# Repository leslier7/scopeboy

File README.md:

# scopeboy
Polished version of the ScopeBoy project started in ECE5730

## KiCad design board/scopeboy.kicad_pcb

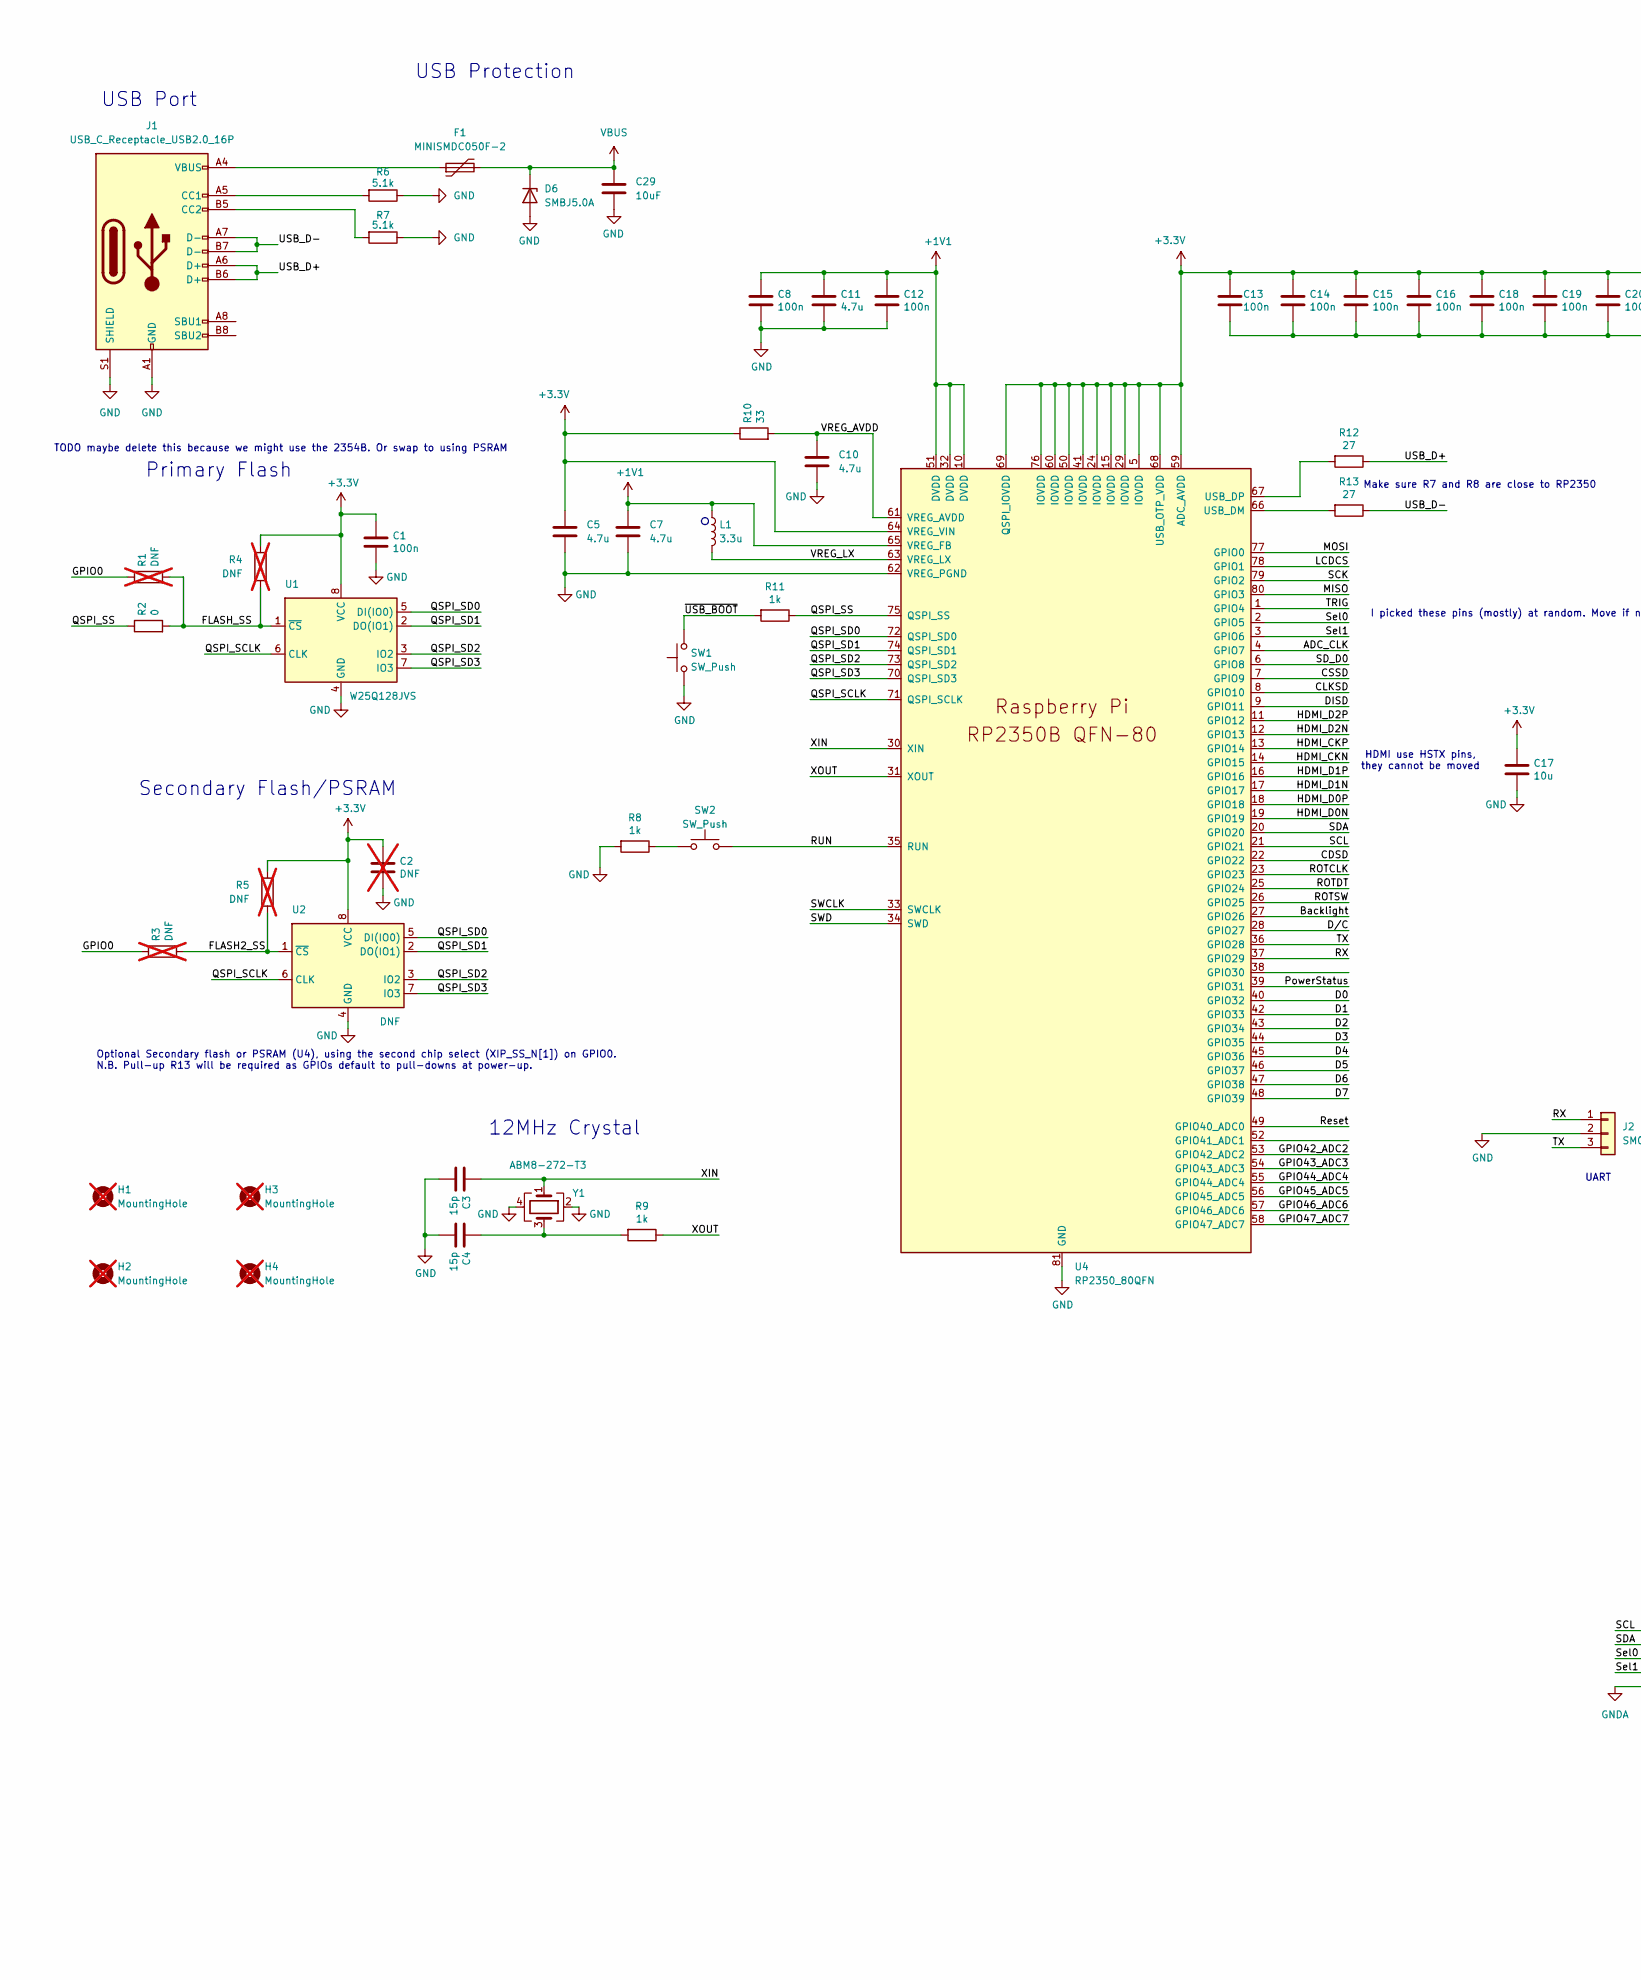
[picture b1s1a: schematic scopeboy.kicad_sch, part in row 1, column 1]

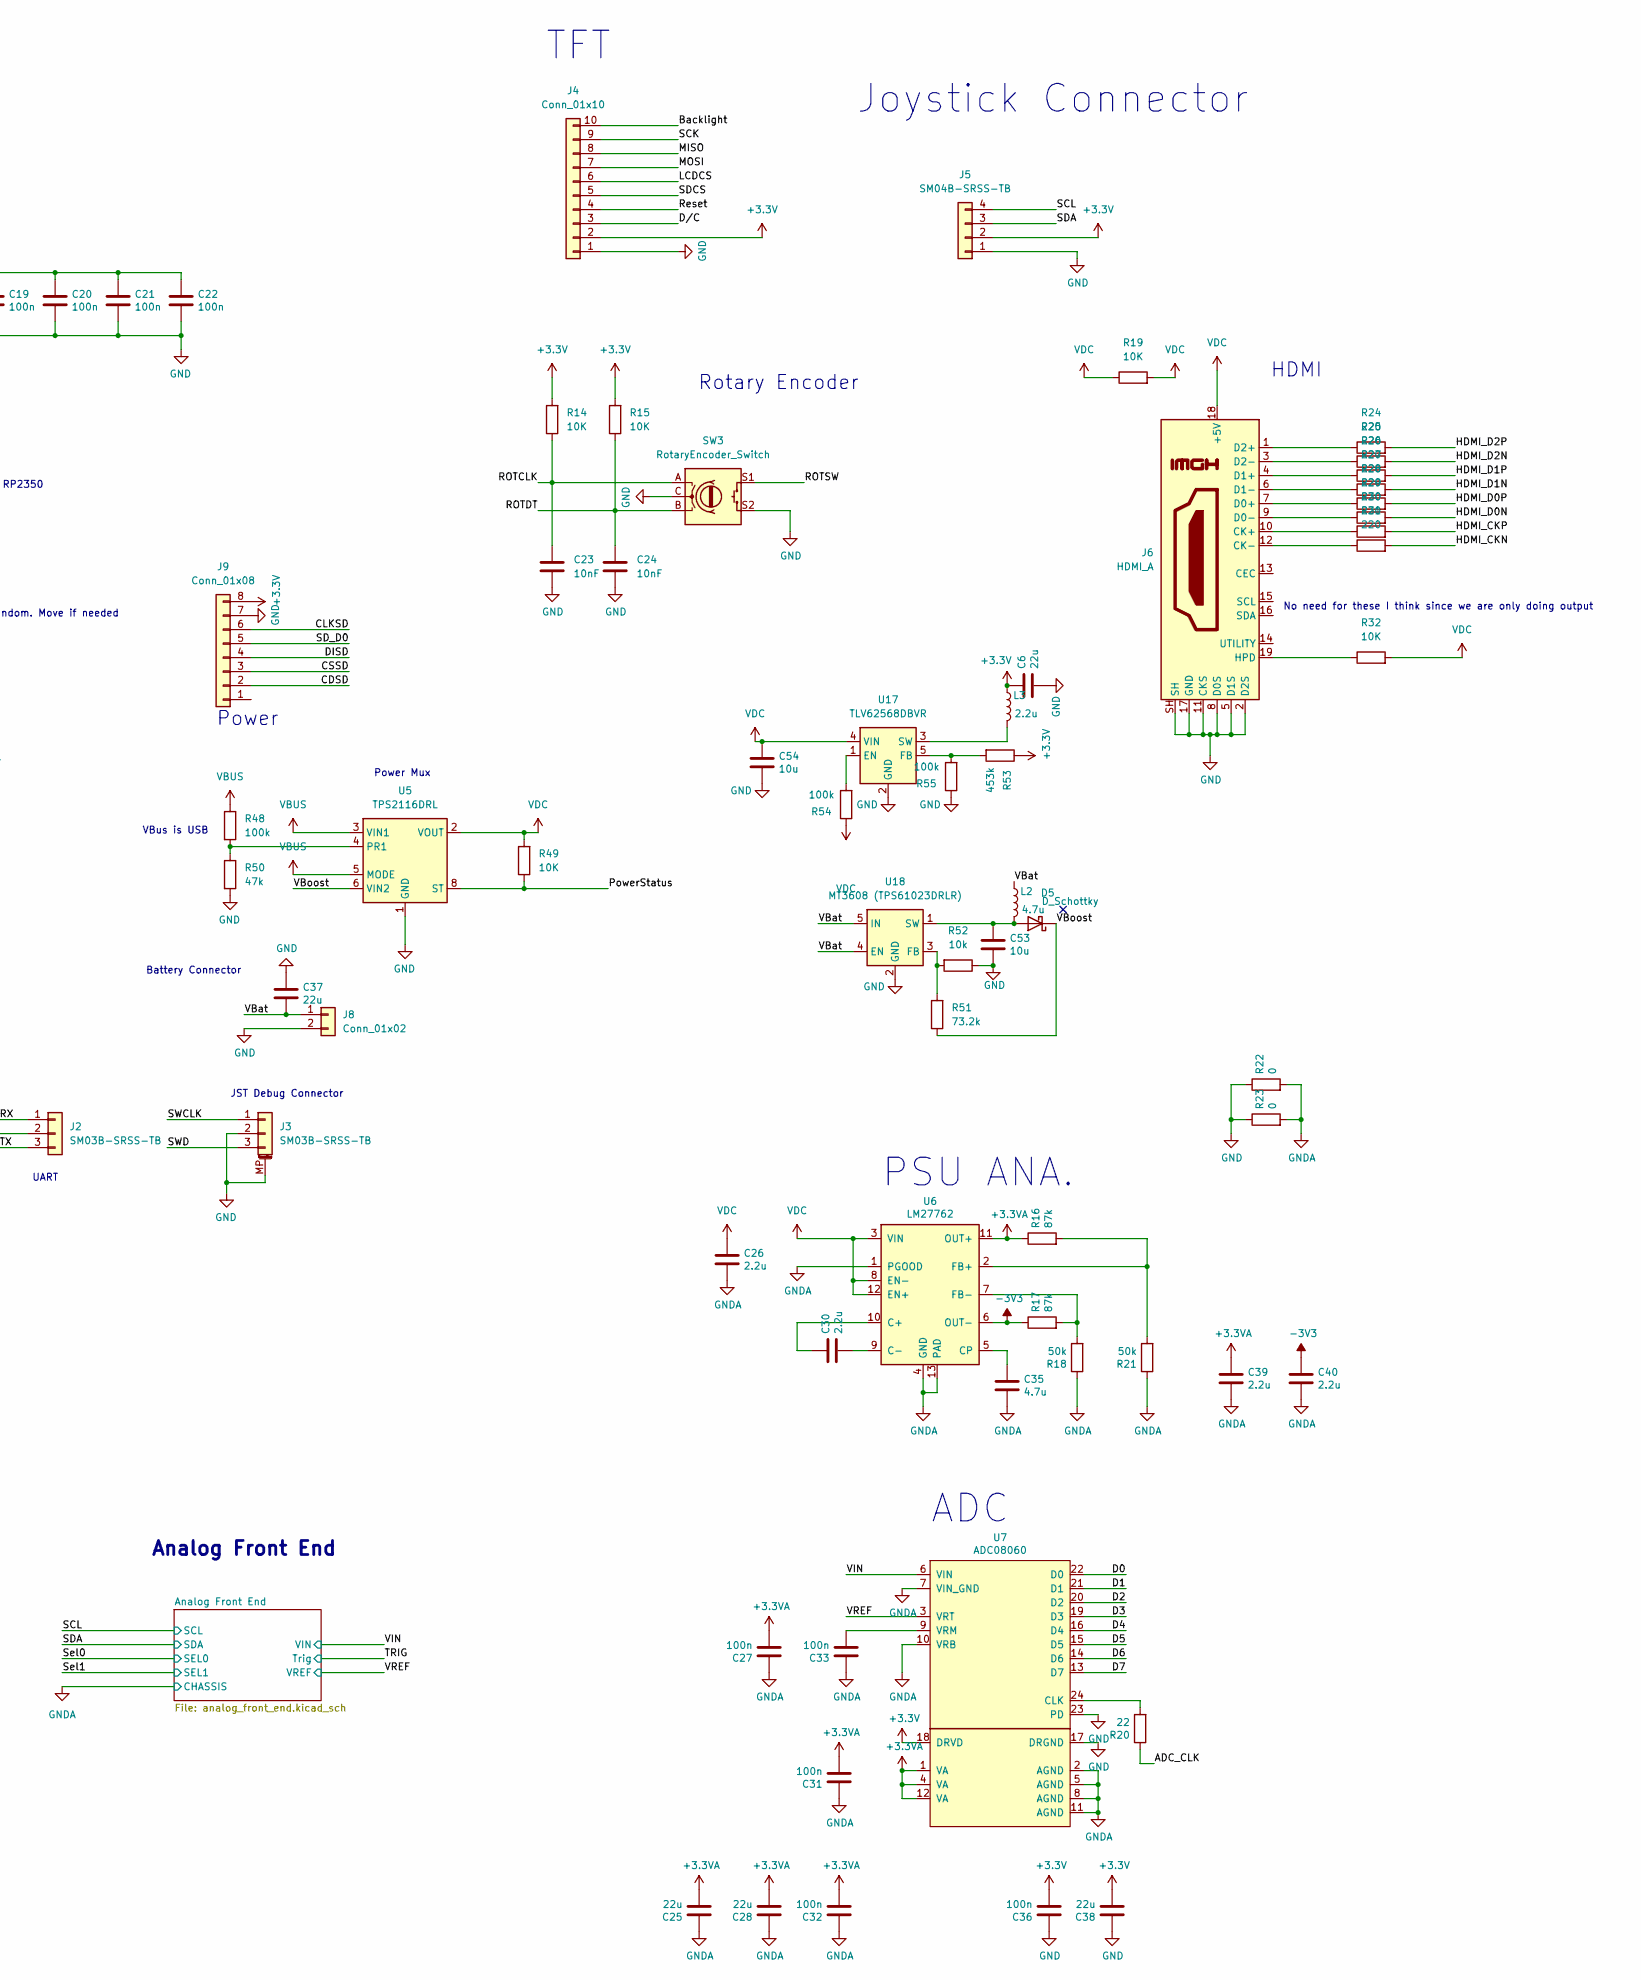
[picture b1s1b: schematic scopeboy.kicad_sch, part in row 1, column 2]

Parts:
C1, C8, C12, C13, C14, C15, C16, C18, C19, C20, C21, C22: 100n; C_0402_1005Metric; MFR. Part # AC0402JRNPO9BN100
C2: DNF; C_0402_1005Metric; not fitted
C3, C4: 15p; C_0402_1005Metric; MFR. Part # GJM1555C1H150GB01D
C5, C7: 4.7u; C_0402_1005Metric_small_pads; MFR. Part # CL05A475MP5NRNC
C6, C37: 22u; C_0805_2012Metric; MFR. Part # CL21A226MQQNNNE
C10, C11: 4.7u; C_0402_1005Metric; MFR. Part # CL05A475MP5NRNC
C17, C53, C54: 10u; C_0805_2012Metric; MFR. Part # CL21A106KOQNNNE
C23, C24: 10nF; C_0603_1608Metric; MFR. Part # CL10B103KB8NNNC; LCSC Part # C1589
C25, C28, C38: 22u; C_0603_1608Metric; MFR. Part # CL10A226MQ8NRNC; LCSC Part # C59461
C26, C30, C39, C40: 2.2u; C_0603_1608Metric; MFR. Part # CL10A225KO8NNNC; LCSC Part # C23630
C27, C31, C32, C33, C36: 100n; C_0603_1608Metric; MFR. Part # CC0603KRX7R9BB104; LCSC Part # C14663
C29: 10uF; C_1206_3216Metric; MFR. Part # TMK316BJ106KL-T
C35: 4.7u; C_0603_1608Metric; MFR. Part # CL10A475KO8NNNC; LCSC Part # C19666
D5: D_Schottky; D_SMA; MFR. Part # SS14
D6: SMBJ5.0A; D_SMB; MFR. Part # SMBJ5.0A
F1: MINISMDC050F-2; Fuse_1812_4532Metric; MFR. Part # MINISMDC050F-2
H1, H2, H3, H4: MountingHole; MountingHole_3.2mm_M3_Pad_TopBottom; not fitted
J1: USB_C_Receptacle_USB2.0_16P; USB_C_Receptacle_GCT_USB4105-xx-A_16P_TopMnt_Horizontal; MFR. Part # USB4105-GF-A
J2: SM03B-SRSS-TB; JST_SH_SM03B-SRSS-TB_1x03-1MP_P1.00mm_Horizontal; MFR. Part # SM03B-SRSS-TB(LF)(SN); LCSC Part # C160403
J3: SM03B-SRSS-TB; JST_SH_SM03B-SRSS-TB_1x03-1MP_P1.00mm_Horizontal
J4: Conn_01x10; PinHeader_1x10_P2.54mm_Vertical
J5: SM04B-SRSS-TB; JST_SH_SM04B-SRSS-TB_1x04-1MP_P1.00mm_Horizontal; MFR. Part # SM04B-SRSS-TB(LF)(SN); LCSC Part # C160404
J6: HDMI_A; HDMI_A_Molex_208658-1001_Horizontal; MFR. Part # 2086581001
J8: Conn_01x02; JST_PH_S2B-PH-SM4-TB_1x02-1MP_P2.00mm_Horizontal; MFR. Part # S2B-PH-SM4-TB(LF)(SN)
J9: Conn_01x08; PinHeader_1x08_P2.54mm_Vertical
L1: 3.3u; L_pol_2016; MFR. Part # SRN4018TA-3R3M
L2: 4.7u; L_Bourns-SRN4018; MFR. Part # SRN4018TA-4R7M
L3: 2.2u; L_Bourns-SRN4018; MFR. Part # SRN4018-2R2M
R1, R3, R4, R5: DNF; R_0402_1005Metric; not fitted
R2: 0; R_0402_1005Metric; MFR. Part # RC0402JR-070RL
R6, R7: 5.1k; R_1206_3216Metric; MFR. Part # CRCW12065K10FKEA
R8, R9, R11: 1k; R_0402_1005Metric; MFR. Part # CRCW04021K00FKED
R10: 33; R_0402_1005Metric; MFR. Part # RC0402JR-0733RL
R12, R13: 27; R_0402_1005Metric; MFR. Part # RC0402JR-0727RL
R14, R15, R19, R32, R49: 10K; R_0603_1608Metric; MFR. Part # RC0603FR-0710KL
R16, R17: 87k; R_0603_1608Metric; MFR. Part # 0603WAF8202T5E; LCSC Part # C23254
R18, R21: 50k; R_0603_1608Metric; MFR. Part # 0603WAF1503T5E; LCSC Part # C22807
R20: 22; R_0603_1608Metric; MFR. Part # 0603WAF220JT5E; LCSC Part # C23345
R22, R23: 0; R_0603_1608Metric; MFR. Part # 0603WAF0000T5E; LCSC Part # C21189
R24, R25, R26, R27, R28, R29, R30, R31: 220; R_0603_1608Metric; MFR. Part # CRGCQ0603J220R
R48, R54, R55: 100k; R_0603_1608Metric; MFR. Part # RC0603FR-07100KL
R50: 47k; R_0603_1608Metric; MFR. Part # RC0603FR-0747KL
R51: 73.2k; R_0603_1608Metric; MFR. Part # RMCF0603FT73K2
R52: 10k; R_0603_1608Metric; MFR. Part # RC0603FR-0710KL
R53: 453k; R_0603_1608Metric; MFR. Part # CRCW0603453KFKEAC
SW1, SW2: SW_Push; SW_Push_1P1T_NO_Vertical_Wuerth_434133025816
SW3: RotaryEncoder_Switch; PEC11L4115FS0020; MFR. Part # PEC11L4115FS0020
U1: W25Q128JVS; SOIC-8_5.23x5.23mm_P1.27mm; MFR. Part # W25Q128JVS
U2: DNF; SOIC-8_5.23x5.23mm_P1.27mm
U4: RP2350_80QFN; RP2350-QFN-80-1EP_10x10_P0.4mm_EP3.4x3.4mm_ThermalVias; MFR. Part # RP2354B
U5: TPS2116DRL; SOT-583-8; MFR. Part # TPS2116DRLR
U6: LM27762; WSON-12-1EP_3x2mm_P0.5mm_EP1x2.65_ThermalVias; MFR. Part # LM27762DSSR; LCSC Part # C473398
U7: ADC08060; TSSOP-24_4.4x7.8mm_P0.65mm; MFR. Part # TI ADC08060CIMT/NOPB; LCSC Part # C701069
U17: TLV62568DBVR; SOT-23-5; MFR. Part # TLV62568DBVR
U18: MT3608 (TPS61023DRLR); SOT-23-6; MFR. Part # MT3608
Y1: ABM8-272-T3; Crystal_SMD_3225-4Pin_3.2x2.5mm; MFR. Part # ABM8-272-T3

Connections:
+1V1: C7.1, C8.1, C11.1, C12.1, L1.1, U4.10 (DVDD), U4.32 (DVDD), U4.51 (DVDD), U4.65 (VREG_FB)
+3.3V: C1.1, C2.1, C5.1, C6.1, C13.1, C14.1, C15.1, C16.1, C17.1, C18.1, C19.1, C20.1, C21.1, C22.1, C36.2, C38.2, J4.2, J5.2, J9.8, L3.1, R4.1, R5.1, R10.1, R14.2, R15.2, R53.1, U1.8 (VCC), U2.8 (VCC), U4.5 (IOVDD), U4.15 (IOVDD), U4.24 (IOVDD), U4.29 (IOVDD), U4.41 (IOVDD), U4.50 (IOVDD), U4.59 (ADC_AVDD), U4.60 (IOVDD), U4.64 (VREG_VIN), U4.68 (USB_OTP_VDD), U4.69 (QSPI_IOVDD), U4.76 (IOVDD), U7.18 (DRVD)
+3.3VA: C25.2, C27.2, C28.2, C31.2, C32.2, C39.1, R16.1, U6.11 (OUT+), U7.1 (VA), U7.4 (VA), U7.12 (VA); also elsewhere on the board
-3V3: C40.1, R17.1, U6.6 (OUT-); also elsewhere on the board
/ADC_CLK: R20.1, U4.4 (GPIO7)
/Backlight: J4.10, U4.27 (GPIO26)
/CDSD: J9.2, U4.22 (GPIO22)
/CLKSD: J9.6, U4.8 (GPIO10)
/CSSD: J9.3, U4.7 (GPIO9)
/D0: U4.40 (GPIO32), U7.22 (D0)
/D1: U4.42 (GPIO33), U7.21 (D1)
/D2: U4.43 (GPIO34), U7.20 (D2)
/D3: U4.44 (GPIO35), U7.19 (D3)
/D4: U4.45 (GPIO36), U7.16 (D4)
/D5: U4.46 (GPIO37), U7.15 (D5)
/D6: U4.47 (GPIO38), U7.14 (D6)
/D7: U4.48 (GPIO39), U7.13 (D7)
/DISD: J9.4, U4.9 (GPIO11)
/D/C: J4.3, U4.28 (GPIO27)
/FLASH2_SS: R3.2, R5.2, U2.1 (~CS)
/FLASH_SS: R1.2, R2.2, R4.2, U1.1 (~CS)
/GPIO0: R1.1, R3.1
/GPIO42_ADC2: U4.53 (GPIO42_ADC2)
/GPIO43_ADC3: U4.54 (GPIO43_ADC3)
/GPIO44_ADC4: U4.55 (GPIO44_ADC4)
/GPIO45_ADC5: U4.56 (GPIO45_ADC5)
/GPIO46_ADC6: U4.57 (GPIO46_ADC6)
/GPIO47_ADC7: U4.58 (GPIO47_ADC7)
/HDMI_CKN: R31.2, U4.14 (GPIO15)
/HDMI_CKP: R30.2, U4.13 (GPIO14)
/HDMI_D0N: R29.2, U4.19 (GPIO19)
/HDMI_D0P: R28.2, U4.18 (GPIO18)
/HDMI_D1N: R27.2, U4.17 (GPIO17)
/HDMI_D1P: R26.2, U4.16 (GPIO16)
/HDMI_D2N: R25.2, U4.12 (GPIO13)
/HDMI_D2P: R24.2, U4.11 (GPIO12)
/LCDCS: J4.6, U4.78 (GPIO1)
/MISO: J4.8, U4.80 (GPIO3)
/MOSI: J4.7, U4.77 (GPIO0)
/PowerStatus: R49.1, U4.39 (GPIO31), U5.8 (ST)
/QSPI_SCLK: U1.6 (CLK), U2.6 (CLK), U4.71 (QSPI_SCLK)
/QSPI_SD0: U1.5 (DI(IO0)), U2.5 (DI(IO0)), U4.72 (QSPI_SD0)
/QSPI_SD1: U1.2 (DO(IO1)), U2.2 (DO(IO1)), U4.74 (QSPI_SD1)
/QSPI_SD2: U1.3 (IO2), U2.3 (IO2), U4.73 (QSPI_SD2)
/QSPI_SD3: U1.7 (IO3), U2.7 (IO3), U4.70 (QSPI_SD3)
/QSPI_SS: R2.1, R11.1, U4.75 (QSPI_SS)
/ROTCLK: C23.1, R14.1, SW3.A, U4.23 (GPIO23)
/ROTDT: C24.1, R15.1, SW3.B, U4.25 (GPIO24)
/ROTSW: SW3.S1, U4.26 (GPIO25)
/RUN: SW2.2, U4.35 (RUN)
/RX: J2.1, U4.37 (GPIO29)
/Reset: J4.4, U4.49 (GPIO40_ADC0)
/SCK: J4.9, U4.79 (GPIO2)
/SCL: J5.4, U4.21 (GPIO21); also elsewhere on the board
/SDA: J5.3, U4.20 (GPIO20); also elsewhere on the board
/SDCS: J4.5
/SD_D0: J9.5, U4.6 (GPIO8)
/SWCLK: J3.1, U4.33 (SWCLK)
/SWD: J3.3, U4.34 (SWD)
/Sel0: U4.2 (GPIO5); also elsewhere on the board
/Sel1: U4.3 (GPIO6); also elsewhere on the board
/TRIG: U4.1 (GPIO4); also elsewhere on the board
/TX: J2.3, U4.36 (GPIO28)
/USB_D+: J1.A6 (D+), J1.B6 (D+), R12.1
/USB_D-: J1.A7 (D-), J1.B7 (D-), R13.1
/VBat: C37.2, J8.1, L2.1, U18.4 (EN), U18.5 (IN)
/VBoost: D5.1 (K), R51.1, U5.6 (VIN2)
/VIN: U7.6 (VIN); also elsewhere on the board
/VREF: U7.3 (VRT); also elsewhere on the board
/VREG_AVDD: C10.1, R10.2, U4.61 (VREG_AVDD)
/VREG_LX: L1.2, U4.63 (VREG_LX)
/XIN: C3.1, U4.30 (XIN), Y1.1
/XOUT: R9.1, U4.31 (XOUT)
/~USB_BOOT: R11.2, SW1.2
GND: C1.2, C2.2, C3.2, C4.2, C5.2, C6.2, C7.2, C8.2, C10.2, C11.2, C12.2, C13.2, C14.2, C15.2, C16.2, C17.2, C18.2, C19.2, C20.2, C21.2, C22.2, C23.2, C24.2, C29.1, C36.1, C37.1, C38.1, C53.2, C54.2, D6.2 (A), J1.A1 (GND), J1.A12 (GND), J1.B1 (GND), J1.B12 (GND), J1.S1 (SHIELD), J2.2, J3.2, J3.MP (MountPin), J4.1, J5.1, J6.2 (D2S), J6.5 (D1S), J6.8 (D0S), J6.11 (CKS), J6.17 (GND), J6.SH, J8.2, J9.7, R6.1, R7.1, R8.2, R22.1, R23.1, R50.2, R52.1, R55.1, SW1.1, SW3.C, SW3.S2, U1.4 (GND), U2.4 (GND), U4.62 (VREG_PGND), U4.81 (GND), U5.1 (GND), U7.17 (DRGND), U7.23 (PD), U17.2 (GND), U18.2 (GND), Y1.2, Y1.4
GNDA: C25.1, C26.2, C27.1, C28.1, C31.1, C32.1, C33.1, C35.2, C39.2, C40.2, R18.1, R21.1, R22.2, R23.2, U6.1 (PGOOD), U6.4 (GND), U6.13 (PAD), U7.2 (AGND), U7.5 (AGND), U7.7 (VIN_GND), U7.8 (AGND), U7.10 (VRB), U7.11 (AGND); also elsewhere on the board
unnamed: C4.1, R9.2, Y1.3
unnamed: C53.1, D5.2 (A), L2.2, U18.1 (SW)
unnamed: F1.1, J1.A4 (VBUS), J1.A9 (VBUS), J1.B4 (VBUS), J1.B9 (VBUS)
unnamed: J1.A5 (CC1), R6.2
unnamed: J1.B5 (CC2), R7.2
unnamed: J6.10 (CK+), R30.1
unnamed: J6.12 (CK-), R31.1
unnamed: J6.7 (D0+), R28.1
unnamed: J6.9 (D0-), R29.1
unnamed: J6.4 (D1+), R26.1
unnamed: J6.6 (D1-), R27.1
unnamed: J6.1 (D2+), R24.1
unnamed: J6.3 (D2-), R25.1
unnamed: J6.19 (HPD), R32.1
unnamed: R8.1, SW2.1
unnamed: R13.2, U4.66 (USB_DM)
unnamed: R12.2, U4.67 (USB_DP)
unnamed: R48.2, R50.1, U5.4 (PR1)
unnamed: C30.1, U6.10 (C+)
unnamed: C30.2, U6.9 (C-)
unnamed: C35.1, U6.5 (CP)
unnamed: R16.2, R21.2, U6.2 (FB+)
unnamed: R17.2, R18.2, U6.7 (FB-)
unnamed: R20.2, U7.24 (CLK)
unnamed: C33.2, U7.9 (VRM)
unnamed: R54.2, U17.1 (EN)
unnamed: R53.2, R55.2, U17.5 (FB)
unnamed: L3.2, U17.3 (SW)
unnamed: R51.2, R52.2, U18.3 (FB)
VBUS: C29.2, D6.1 (K), F1.2, R48.1, U5.3 (VIN1), U5.5 (MODE)
VDC: C26.1, C54.1, J6.18 (+5V), R19.1, R19.2, R32.2, R49.2, R54.1, U5.2 (VOUT), U5.7 (VOUT), U6.3 (VIN), U6.8 (EN-), U6.12 (EN+), U17.4 (VIN)

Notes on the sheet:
Optional Secondary flash or PSRAM (U4), using the second chip select (XIP_SS_N[1]) on GPIO0. N.B. Pull-up R13 will be required as GPIOs default to pull-downs at power-up.
Rotary Encoder
12MHz Crystal
Power Mux
I picked these pins (mostly) at random. Move if needed
ADC
PSU ANA.
Joystick Connector
Primary Flash
USB Protection
Battery Connector
No need for these I think since we are only doing output
TFT
HDMI use HSTX pins, they cannot be moved
JST Debug Connector
Make sure R7 and R8 are close to RP2350
Analog Front End
Secondary Flash/PSRAM
TODO maybe delete this because we might use the 2354B. Or swap to using PSRAM
VBus is USB
UART
USB Port
Power
HDMI

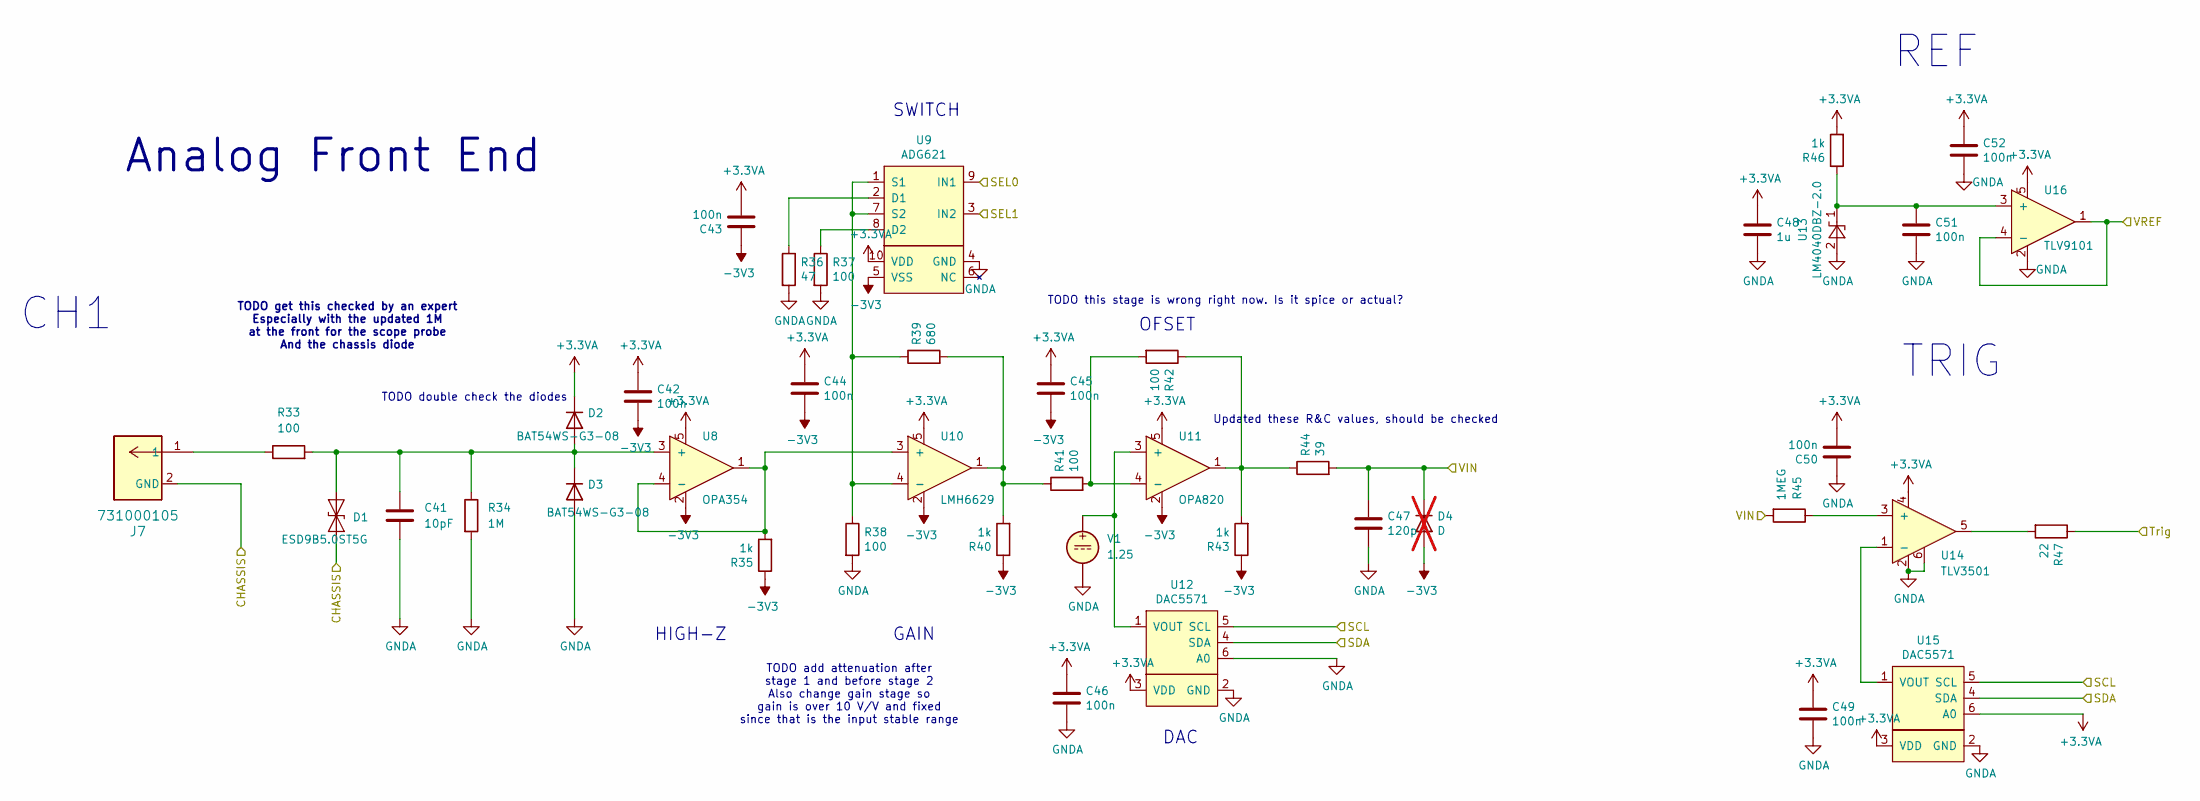
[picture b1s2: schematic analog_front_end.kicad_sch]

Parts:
C41: 10pF; C_0603_1608Metric; MFR. Part # C0603C100J5GACTU
C42, C43, C44, C45, C46, C49, C50, C51, C52: 100n; C_0603_1608Metric; MFR. Part # CC0603KRX7R9BB104; LCSC Part # C14663
C47: 120p; C_0603_1608Metric; MFR. Part # FN18X104K160PSG
C48: 1u; C_0603_1608Metric; MFR. Part # CL10A105KB8NNNC; LCSC Part # C15849
D1: ESD9B5.0ST5G; D_SOD-923; MFR. Part # ESD9B5.0ST5G
D2, D3: BAT54WS-G3-08; D_0603_1608Metric; MFR. Part # BAT54WS-E3-08
D4: D; D_0603_1608Metric; not fitted
J7: 731000105; CONN_73100-0105_MOL; MFR. Part # 731000105
R33: 100; R_0603_1608Metric; MFR. Part # ERJ-3EKF1000V
R34: 1M; R_0603_1608Metric; MFR. Part # RC0603FR-071ML
R35, R40, R43, R46: 1k; R_0603_1608Metric; MFR. Part # 0603WAF1001T5E; LCSC Part # C21190
R36: 47; R_0603_1608Metric; MFR. Part # 0603WAF470JT5E; LCSC Part # C23182
R37, R38, R41, R42: 100; R_0603_1608Metric; MFR. Part # ERJ-3EKF1000V; LCSC Part # C22775
R39: 680; R_0603_1608Metric; MFR. Part # 0603WAF6801T5E; LCSC Part # C23212
R44: 39; R_0603_1608Metric; MFR. Part # 0603WAF1000T5E
R45: 1MEG; R_0603_1608Metric; MFR. Part # ERJ3EKF1004V; LCSC Part # C193390
R47: 22; R_0603_1608Metric; MFR. Part # 0603WAF220JT5E; LCSC Part # C23345
U8: OPA354; SOT-23-5; MFR. Part # OPA354AIDBVR; LCSC Part # C36384
U9: ADG621; MSOP-10_3x3mm_P0.5mm; MFR. Part # ADG621BRMZ; LCSC Part # C208597
U10: LMH6629; SOT-23-5; MFR. Part # LMH6629MFX/NOPB; LCSC Part # C206003
U11: OPA820; SOT-23-5; MFR. Part # OPA830IDBVR; LCSC Part # C2058414
U12, U15: DAC5571; SOT-23-6; MFR. Part # DAC5571IDBVT; LCSC Part # C24061
U13: LM4040DBZ-2.0; SOT-23; MFR. Part # LM4040A20IDBZR; LCSC Part # C127070
U14: TLV3501; SOT-23-6; MFR. Part # TLV3501AIDBVT; LCSC Part # C193413
U16: TLV9101; SOT-23-5; MFR. Part # TLV9101IDBVR; LCSC Part # C4368903
V1: 1.25

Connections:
+3.3VA: C42.1, C43.2, C44.1, C45.1, C46.1, C48.1, C49.1, C50.2, C52.1, D2.1 (K), R46.2, U8.5, U9.10 (VDD), U10.5, U11.5, U12.3 (VDD), U14.4, U15.3 (VDD), U15.6 (A0), U16.5; also elsewhere on the board
-3V3: C42.2, C43.1, C44.2, C45.2, D4.2 (A), R35.1, R40.1, R43.1, U8.2, U9.5 (VSS), U10.2, U11.2; also elsewhere on the board
/SCL: U12.5 (SCL), U15.5 (SCL); also elsewhere on the board
/SDA: U12.4 (SDA), U15.4 (SDA); also elsewhere on the board
/Sel0: U9.9 (IN1); also elsewhere on the board
/Sel1: U9.3 (IN2); also elsewhere on the board
/TRIG: R47.1; also elsewhere on the board
/VIN: C47.1, D4.1 (K), R44.2, R45.2; also elsewhere on the board
/VREF: U16.1, U16.4 (-); also elsewhere on the board
GNDA: C41.2, C46.2, C47.2, C48.2, C49.2, C50.1, C51.2, C52.2, D1.2 (A2), D3.2 (A), J7.2 (GND), R34.2, R36.2, R37.2, R38.2, U9.4 (GND), U12.2 (GND), U12.6 (A0), U13.2 (A), U14.2, U14.6, U15.2 (GND), U16.2, V1.2; also elsewhere on the board
unnamed: C41.1, D1.1 (A1), D2.2 (A), D3.1 (K), R33.2, R34.1, U8.3 (+)
unnamed: J7.1, R33.1
unnamed: R39.2, R40.2, R41.1, U10.1
unnamed: R42.1, R43.2, R44.1, U11.1
unnamed: R47.2, U14.5
unnamed: R36.1, U9.2 (D1)
unnamed: R37.1, U9.8 (D2)
unnamed: R35.2, U8.1, U8.4 (-), U10.3 (+)
unnamed: R38.1, R39.1, U9.1 (S1), U9.7 (S2), U10.4 (-)
unnamed: U11.3 (+), U12.1 (VOUT), V1.1
unnamed: R41.2, R42.2, U11.4 (-)
unnamed: C51.1, R46.1, U13.1 (K), U16.3 (+)
unnamed: R45.1, U14.3 (+)
unnamed: U14.1 (-), U15.1 (VOUT)

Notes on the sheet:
TODO this stage is wrong right now. Is it spice or actual?
DAC
TODO add attenuation after stage 1 and before stage 2 Also change gain stage so gain is over 10 V/V and fixed since that is the input stable range
GAIN
REF
SWITCH
TODO get this checked by an expert Especially with the updated 1M at the front for the scope probe And the chassis diode
Updated these R&C values, should be checked
HIGH-Z
TODO double check the diodes
TRIG
CH1
OFSET
Analog Front End

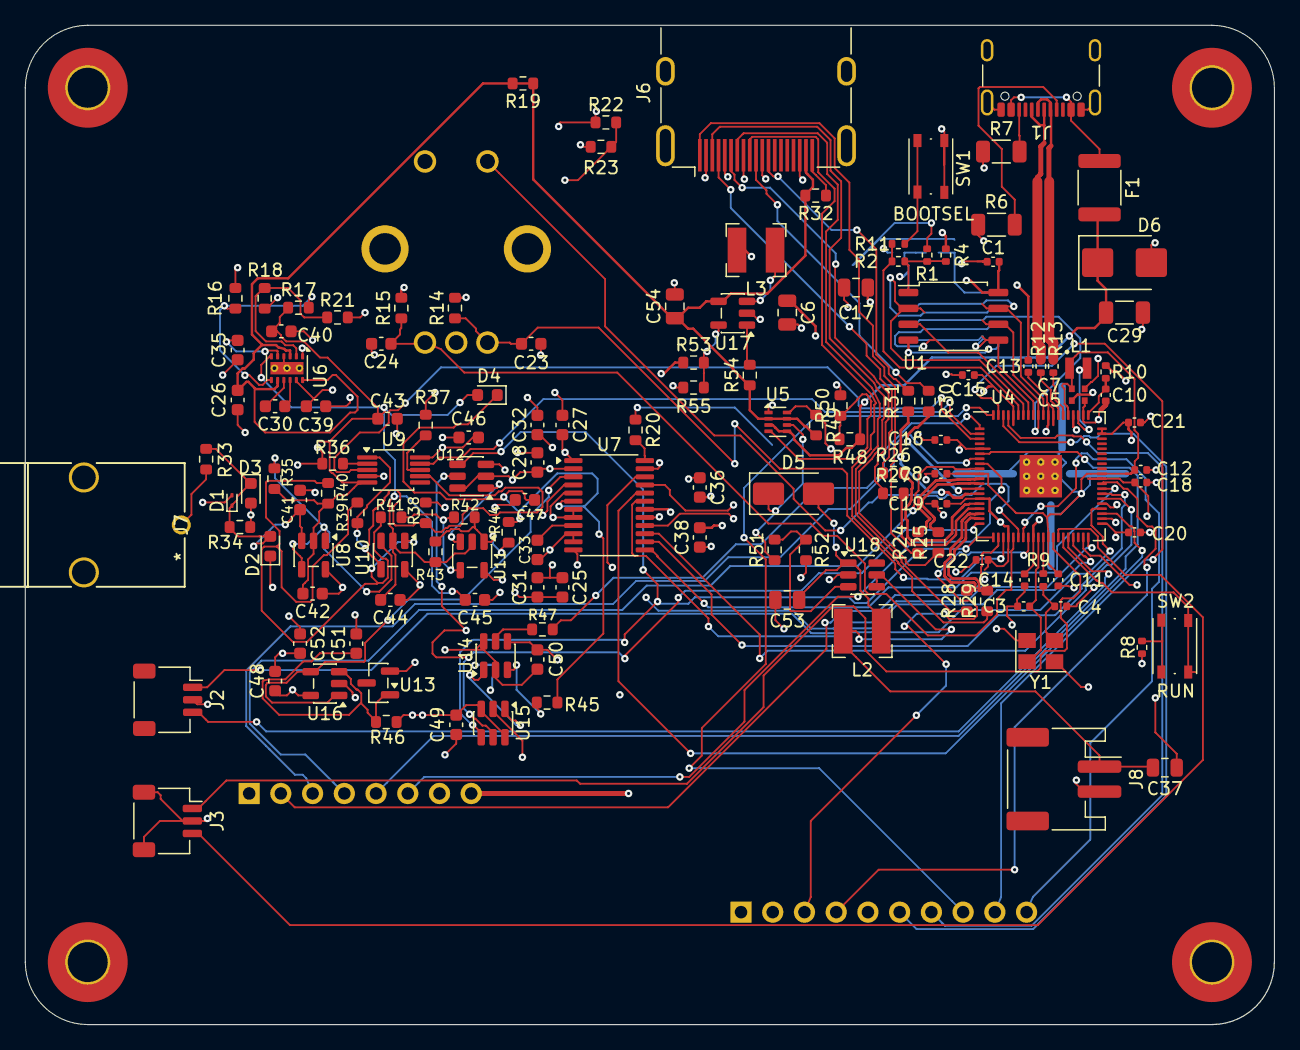
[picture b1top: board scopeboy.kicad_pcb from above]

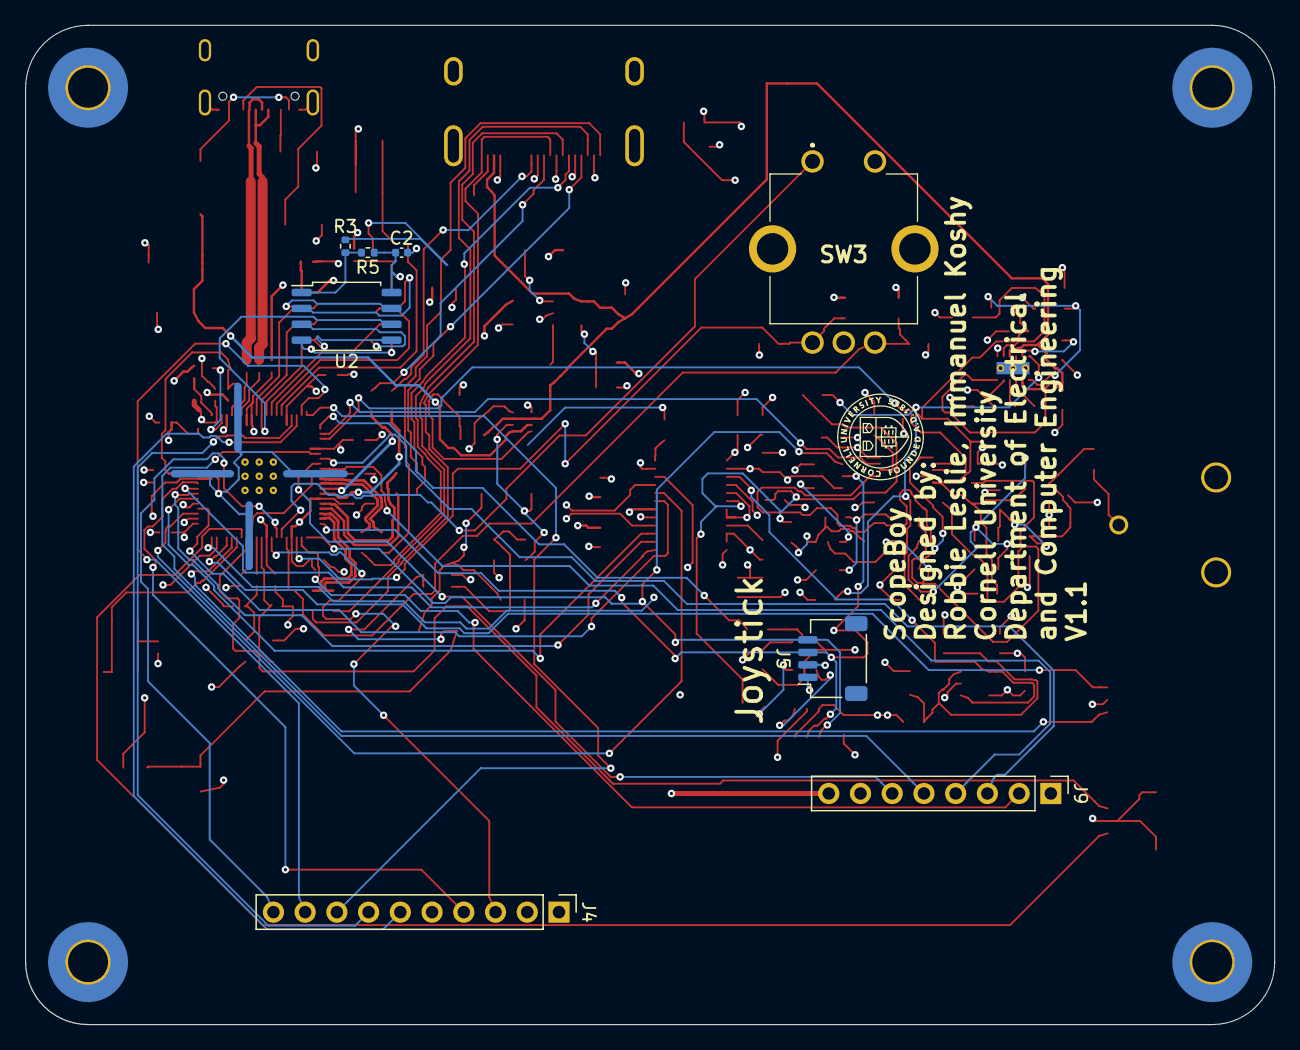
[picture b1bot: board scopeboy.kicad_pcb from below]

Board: 4 copper layers, 100.0 x 80.0 mm, 151 parts (8 on the bottom side), 114 nets.

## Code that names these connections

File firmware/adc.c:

// Code by Robbie Leslie

#include "adc.h"
#include "pico/stdlib.h"
#include "hardware/dma.h"
#include "hardware/pio.h"
#include "adc8060.pio.h"
#include "dac.h"

// Analog mux gain select pins
#define SEL_0 5
#define SEL_1 6

// First GPIO of the 8-bit parallel data bus (D0=GPIO32 … D7=GPIO39)
#define D_BUS_FIRST_PIN 32

// CLK output to ADC8060
#define ADC_CLK_PIN 9

uint8_t capture_buf[CAPTURE_DEPTH];
uint8_t frame_buf[CAPTURE_DEPTH];

volatile bool trigger_fired = false;
volatile bool capture_ready = false;
volatile bool trigger_armed = true;

// Pointer reset value for the DMA control channel
uint8_t *dma_address_pointer = &capture_buf[0];

void init_adc_capture() {
    // Set up analog mux gain select pins
    gpio_init(SEL_0);
    gpio_set_dir(SEL_0, GPIO_OUT);
    gpio_init(SEL_1);
    gpio_set_dir(SEL_1, GPIO_OUT);

    // PIO1 — TFTMaster already owns pio0
    // Generates CLK on GPIO9 and captures D0-D7 (GPIO32-39) on each rising edge
    PIO pio = pio1;
    uint sm = pio_claim_unused_sm(pio, true);
    uint offset = pio_add_program(pio, &adc8060_capture_program);
    adc8060_capture_program_init(pio, sm, offset, ADC_CLK_PIN, D_BUS_FIRST_PIN, SAMPLE_RATE_HZ);

    uint ctrl_chan = dma_claim_unused_channel(true);
    uint data_chan = dma_claim_unused_channel(true);

    // Control channel: resets the data channel's write address so capture loops
    dma_channel_config c = dma_channel_get_default_config(ctrl_chan);
    channel_config_set_transfer_data_size(&c, DMA_SIZE_32);
    channel_config_set_read_increment(&c, false);
    channel_config_set_write_increment(&c, false);
    channel_config_set_chain_to(&c, data_chan);

    dma_channel_configure(
        ctrl_chan,
        &c,
        &dma_hw->ch[data_chan].write_addr,
        &dma_address_pointer,
        1,
        false
    );

    // Data channel: 8-bit reads from PIO RX FIFO → capture_buf, paced by PIO DREQ
    dma_channel_config cfg = dma_channel_get_default_config(data_chan);
    channel_config_set_transfer_data_size(&cfg, DMA_SIZE_8);
    channel_config_set_read_increment(&cfg, false);
    channel_config_set_write_increment(&cfg, true);
    channel_config_set_dreq(&cfg, pio_get_dreq(pio, sm, false));
    channel_config_set_chain_to(&cfg, ctrl_chan);

    dma_channel_configure(
        data_chan,
        &cfg,
        capture_buf,
        (volatile uint8_t *)&pio->rxf[sm],
        CAPTURE_DEPTH,
        true
    );

    dma_start_channel_mask(1u << ctrl_chan);
}

float adc_to_volt(uint8_t adc_val) {
    return (adc_val / 255.0f) * 3.3f;
}

void set_gain(gain_mode_t gain) {
    switch (gain) {
        case GAIN_LOW:
            gpio_put(SEL_0, false);
            gpio_put(SEL_1, false);
            break;
        case GAIN_MEDIUM:
            gpio_put(SEL_0, false);
            gpio_put(SEL_1, true);
            break;
        case GAIN_HIGH:
            gpio_put(SEL_0, true);
            gpio_put(SEL_1, false);
            break;
        default:
            gpio_put(SEL_0, false);
            gpio_put(SEL_1, false);
            break;
    }
}

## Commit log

2026-02-20 Minimal RP2350B board
2026-02-27 Continued schematic moving from old version to new version
2026-03-04 Fixed MFR label and added more TOOD
2026-03-06 More TODO notes and swaped ref op amp
2026-03-06 Added TODO for 5V charge pump
2026-03-06 HDMI to HSTX GPIO pins, and more TODOs
2026-03-13 Added spice circuit models
2026-03-13 Working on simulation for front end
2026-03-19 Got first version of front end sim working
2026-03-20 More work on front end circuit, and GPIO connections
2026-04-16 Merged footprints, need to do schematic merge
2026-04-16 Re-moved with back side
2026-04-17 All components in layout
2026-04-17 Positioned boards at same place
2026-04-17 Replaced copper with vias
2026-04-17 Started placement
2026-04-17 New merge placemetn
2026-04-17 Updated trig, sel0, sel1 pins
2026-04-17 Added battery JST connector
2026-04-19 Added power mux and USB protection
2026-04-20 Updated board with new power system
2026-04-20 Converted layer to power
2026-04-20 Updated the board stackup
2026-04-20 Removed TODO comments
2026-05-11 Production version of board
2026-05-12 Started work on firmware
2026-05-13 Added the pico-hdmi library
2026-05-13 Updated the DAC behavior
2026-05-13 Added HDMI task list
2026-05-13 Started HDMI implementation
2026-05-14 More work on HDMI firmware
2026-05-14 Fixing reset on TFT
2026-05-14 Fixed joystick qwiic connector bug
2026-05-14 Started work on fixing PCB bugs
2026-05-14 Added updated ADC code
